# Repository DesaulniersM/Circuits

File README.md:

# Circuits
A place to store circuits and PCB versions

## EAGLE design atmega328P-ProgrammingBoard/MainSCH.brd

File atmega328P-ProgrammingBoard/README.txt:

These files are for a board made to program an Atmega328p.

The PCBWayCam folder holds the gerber files used to actually get the board produced.

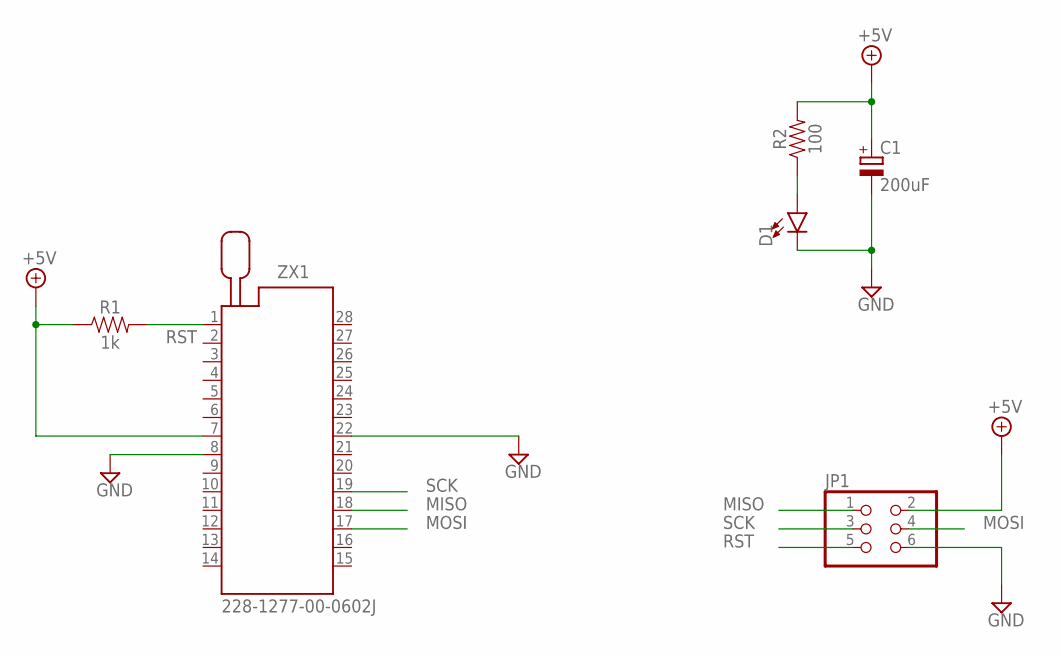
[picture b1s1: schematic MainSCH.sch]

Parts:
C1: 200uF; E2,5-6
D1: LED0603; LED-0603
JP1: PINHD-2X3; 2X03
R1: 1k; 0603
R2: 100; 0603
ZX1: 228-1277-00-0602J

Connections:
+5V: C1.+, JP1.2, R1.1, R2.2, ZX1.7
GND: C1.-, D1.C, JP1.6, ZX1.8, ZX1.22
MISO: JP1.1, ZX1.18
MOSI: JP1.4, ZX1.17
unnamed: D1.A, R2.1
RST: JP1.5, R1.2, ZX1.1
SCK: JP1.3, ZX1.19

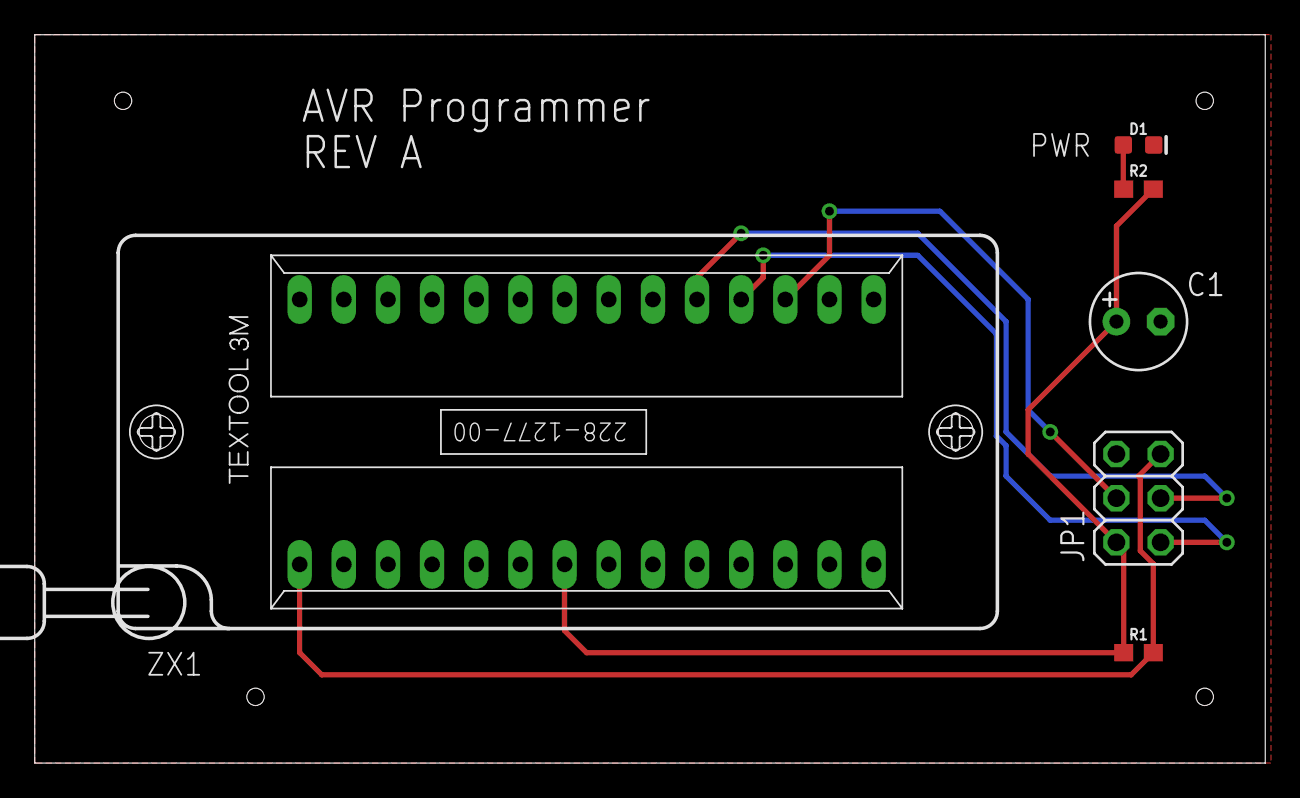
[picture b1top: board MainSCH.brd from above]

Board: 2 copper layers, 70.8 x 41.9 mm, 6 parts (0 on the bottom side), 7 nets.

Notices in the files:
parts and their libraries:
SparkFun-LED: Licensing: Creative Commons ShareAlike 4.0 International - https://creativecommons.org/licenses/by-sa/4.0
